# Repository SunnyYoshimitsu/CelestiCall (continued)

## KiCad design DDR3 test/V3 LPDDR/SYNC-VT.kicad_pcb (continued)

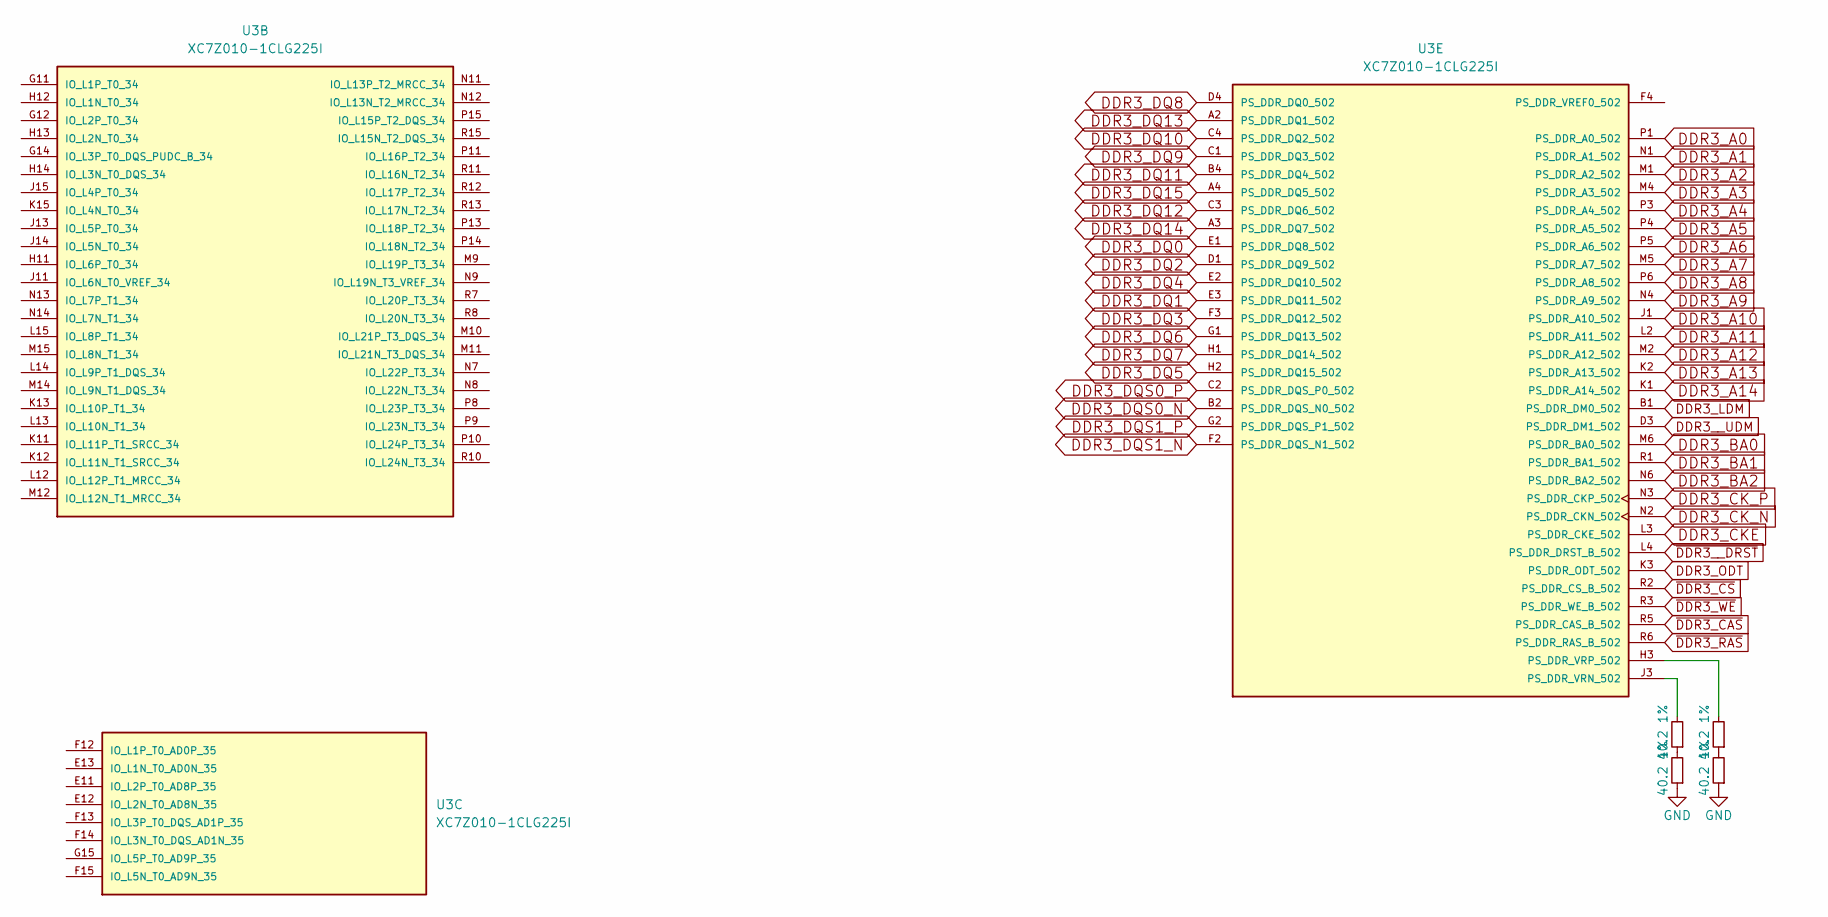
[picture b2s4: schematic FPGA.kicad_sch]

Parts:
R60, R61, R62, R63: 40.2 1%; R_0201_0603Metric; MPN RC0402FR-0740R2L
U3: XC7Z010-1CLG225I; 225-LFBGA; MPN XC7Z010-1CLG225I

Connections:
DDR3_A0: U3.P1 (PS_DDR_A0_502); also elsewhere on the board
DDR3_A1: U3.N1 (PS_DDR_A1_502); also elsewhere on the board
DDR3_A2: U3.M1 (PS_DDR_A2_502); also elsewhere on the board
DDR3_A3: U3.M4 (PS_DDR_A3_502); also elsewhere on the board
DDR3_A4: U3.P3 (PS_DDR_A4_502); also elsewhere on the board
DDR3_A5: U3.P4 (PS_DDR_A5_502); also elsewhere on the board
DDR3_A6: U3.P5 (PS_DDR_A6_502); also elsewhere on the board
DDR3_A7: U3.M5 (PS_DDR_A7_502); also elsewhere on the board
DDR3_A8: U3.P6 (PS_DDR_A8_502); also elsewhere on the board
DDR3_A9: U3.N4 (PS_DDR_A9_502); also elsewhere on the board
DDR3_A10: U3.J1 (PS_DDR_A10_502); also elsewhere on the board
DDR3_A11: U3.L2 (PS_DDR_A11_502); also elsewhere on the board
DDR3_A12: U3.M2 (PS_DDR_A12_502); also elsewhere on the board
DDR3_A13: U3.K2 (PS_DDR_A13_502); also elsewhere on the board
DDR3_A14: U3.K1 (PS_DDR_A14_502)
DDR3_BA0: U3.M6 (PS_DDR_BA0_502); also elsewhere on the board
DDR3_BA1: U3.R1 (PS_DDR_BA1_502); also elsewhere on the board
DDR3_BA2: U3.N6 (PS_DDR_BA2_502)
DDR3_CKE: U3.L3 (PS_DDR_CKE_502); also elsewhere on the board
DDR3_CK_N: U3.N2 (PS_DDR_CKN_502); also elsewhere on the board
DDR3_CK_P: U3.N3 (PS_DDR_CKP_502); also elsewhere on the board
DDR3_DQ0: U3.E1 (PS_DDR_DQ8_502); also elsewhere on the board
DDR3_DQ1: U3.E3 (PS_DDR_DQ11_502); also elsewhere on the board
DDR3_DQ2: U3.D1 (PS_DDR_DQ9_502); also elsewhere on the board
DDR3_DQ3: U3.F3 (PS_DDR_DQ12_502); also elsewhere on the board
DDR3_DQ4: U3.E2 (PS_DDR_DQ10_502); also elsewhere on the board
DDR3_DQ5: U3.H2 (PS_DDR_DQ15_502); also elsewhere on the board
DDR3_DQ6: U3.G1 (PS_DDR_DQ13_502); also elsewhere on the board
DDR3_DQ7: U3.H1 (PS_DDR_DQ14_502); also elsewhere on the board
DDR3_DQ8: U3.D4 (PS_DDR_DQ0_502); also elsewhere on the board
DDR3_DQ9: U3.C1 (PS_DDR_DQ3_502); also elsewhere on the board
DDR3_DQ10: U3.C4 (PS_DDR_DQ2_502); also elsewhere on the board
DDR3_DQ11: U3.B4 (PS_DDR_DQ4_502); also elsewhere on the board
DDR3_DQ12: U3.C3 (PS_DDR_DQ6_502); also elsewhere on the board
DDR3_DQ13: U3.A2 (PS_DDR_DQ1_502); also elsewhere on the board
DDR3_DQ14: U3.A3 (PS_DDR_DQ7_502); also elsewhere on the board
DDR3_DQ15: U3.A4 (PS_DDR_DQ5_502); also elsewhere on the board
DDR3_DQS0_N: U3.B2 (PS_DDR_DQS_N0_502)
DDR3_DQS0_P: U3.C2 (PS_DDR_DQS_P0_502); also elsewhere on the board
DDR3_DQS1_N: U3.F2 (PS_DDR_DQS_N1_502)
DDR3_DQS1_P: U3.G2 (PS_DDR_DQS_P1_502); also elsewhere on the board
DDR3_LDM: U3.B1 (PS_DDR_DM0_502); also elsewhere on the board
DDR3_ODT: U3.K3 (PS_DDR_ODT_502)
DDR3__UDM: U3.D3 (PS_DDR_DM1_502); also elsewhere on the board
GND: R61.1, R63.1; also elsewhere on the board
unnamed: R60.1, R61.2
unnamed: R62.1, R63.2
unnamed: R60.2, U3.J3 (PS_DDR_VRN_502)
unnamed: R62.2, U3.H3 (PS_DDR_VRP_502)
~DDR3_CAS: U3.R5 (PS_DDR_CAS_B_502); also elsewhere on the board
~DDR3_CS: U3.R2 (PS_DDR_CS_B_502); also elsewhere on the board
~DDR3_RAS: U3.R6 (PS_DDR_RAS_B_502); also elsewhere on the board
~DDR3_WE: U3.R3 (PS_DDR_WE_B_502); also elsewhere on the board
~DDR3__DRST: U3.L4 (PS_DDR_DRST_B_502)

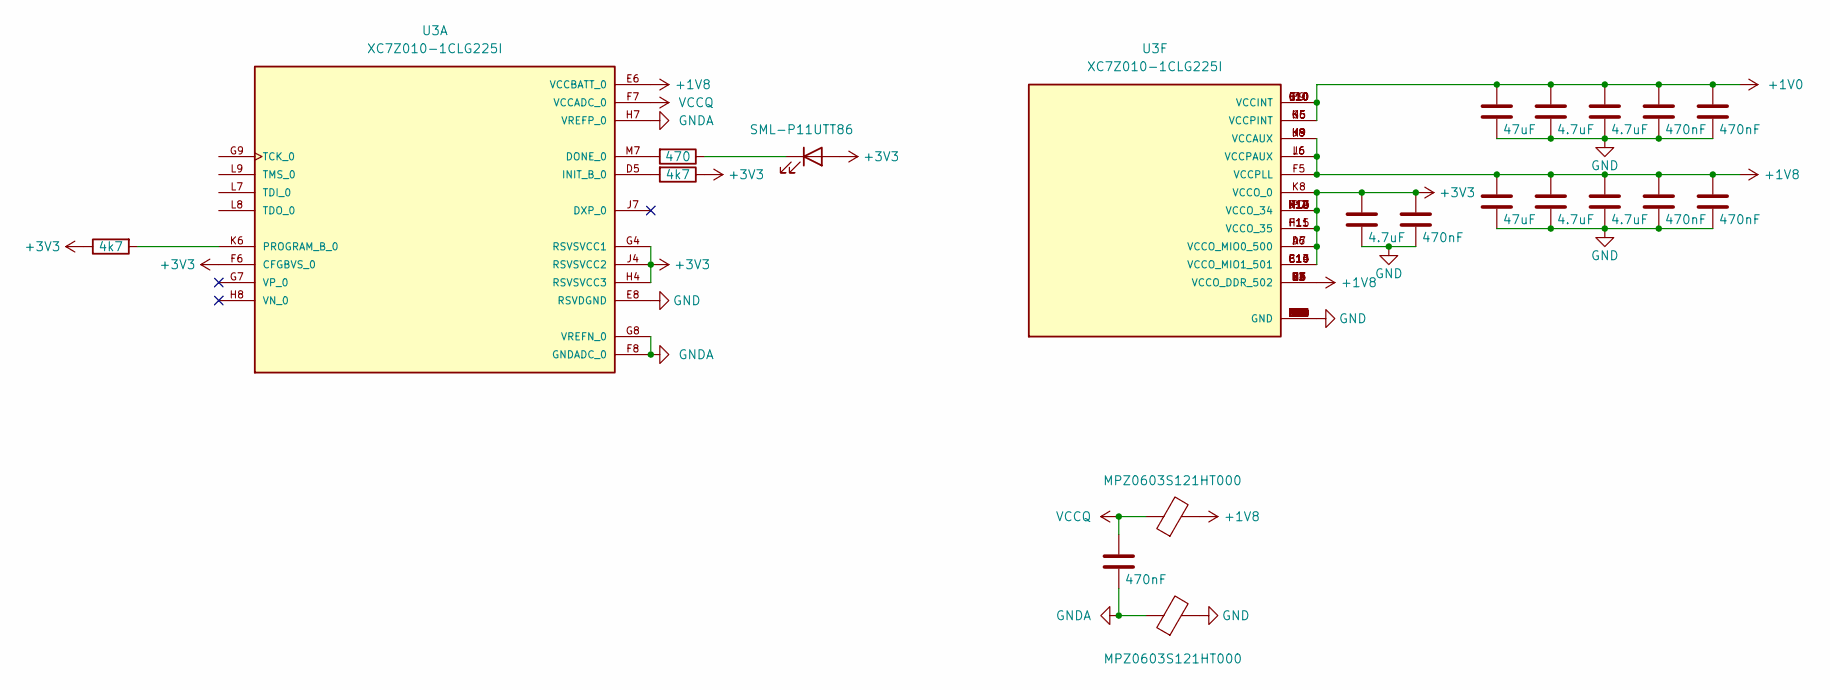
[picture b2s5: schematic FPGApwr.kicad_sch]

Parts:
C13, C19: 47uF; C_0805_2012Metric
C14, C16, C20, C21, C24: 4.7uF; C_0201_0603Metric
C15, C17, C18, C22, C23, C25: 470nF; C_0201_0603Metric
D1: SML-P11UTT86; LED_0402_1005Metric
FB1, FB2: MPZ0603S121HT000; C_0201_0603Metric
R11, R12: 4k7; C_0201_0603Metric
R13: 470; C_0201_0603Metric
U3: XC7Z010-1CLG225I; 225-LFBGA; MPN XC7Z010-1CLG225I

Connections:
+1V0: C19.1, C20.1, C21.1, C22.1, C23.1, U3.E10 (VCCINT), U3.F9 (VCCINT), U3.G6 (VCCPINT), U3.G10 (VCCINT), U3.H5 (VCCPINT), U3.J10 (VCCINT), U3.K5 (VCCPINT), U3.L10 (VCCINT); also elsewhere on the board
+1V8: C13.1, C14.1, C15.1, C16.1, C17.1, FB1.2, U3.B3 (VCCO_DDR_502), U3.E4 (VCCO_DDR_502), U3.E6 (VCCBATT_0), U3.F1 (VCCO_DDR_502), U3.F5 (VCCPLL), U3.H9 (VCCAUX), U3.J2 (VCCO_DDR_502), U3.J6 (VCCPAUX), U3.J8 (VCCAUX), U3.K9 (VCCAUX), U3.L6 (VCCPAUX), U3.M3 (VCCO_DDR_502), U3.R4 (VCCO_DDR_502); also elsewhere on the board
+3V3: C24.1, C25.1, D1.2 (A), R11.1, R12.1, U3.A6 (VCCO_MIO0_500), U3.B13 (VCCO_MIO1_501), U3.C10 (VCCO_MIO1_501), U3.D7 (VCCO_MIO0_500), U3.E14 (VCCO_MIO1_501), U3.F6 (CFGBVS_0), U3.F11 (VCCO_35), U3.G4 (RSVSVCC1), U3.H4 (RSVSVCC3), U3.H15 (VCCO_35), U3.J4 (RSVSVCC2), U3.J12 (VCCO_34), U3.K8 (VCCO_0), U3.M13 (VCCO_34), U3.N10 (VCCO_34), U3.P7 (VCCO_34), U3.R14 (VCCO_34); also elsewhere on the board
GND: C13.2, C14.2, C15.2, C16.2, C17.2, C19.2, C20.2, C21.2, C22.2, C23.2, C24.2, C25.2, FB2.2, U3.A1 (GND), U3.A11 (GND), U3.B8 (GND), U3.C5 (GND), U3.C15 (GND), U3.D2 (GND), U3.D12 (GND), U3.E5 (GND), U3.E7 (GND), U3.E8 (RSVDGND), U3.E9 (GND), U3.F10 (GND), U3.G3 (GND), U3.G5 (GND), U3.G13 (GND), U3.H6 (GND), U3.H10 (GND), U3.J5 (GND), U3.J9 (GND), U3.K4 (GND), U3.K7 (GND), U3.K10 (GND), U3.K14 (GND), U3.L1 (GND), U3.L5 (GND), U3.L11 (GND), U3.M8 (GND), U3.N5 (GND), U3.N15 (GND), U3.P2 (GND), U3.P12 (GND), U3.R9 (GND); also elsewhere on the board
GNDA: C18.2, FB2.1, U3.F8 (GNDADC_0), U3.G8 (VREFN_0), U3.H7 (VREFP_0)
unnamed: D1.1 (K), R13.1
unnamed: R13.2, U3.M7 (DONE_0)
unnamed: R11.2, U3.D5 (INIT_B_0)
unnamed: R12.2, U3.K6 (PROGRAM_B_0)
VCCQ: C18.1, FB1.1, U3.F7 (VCCADC_0)

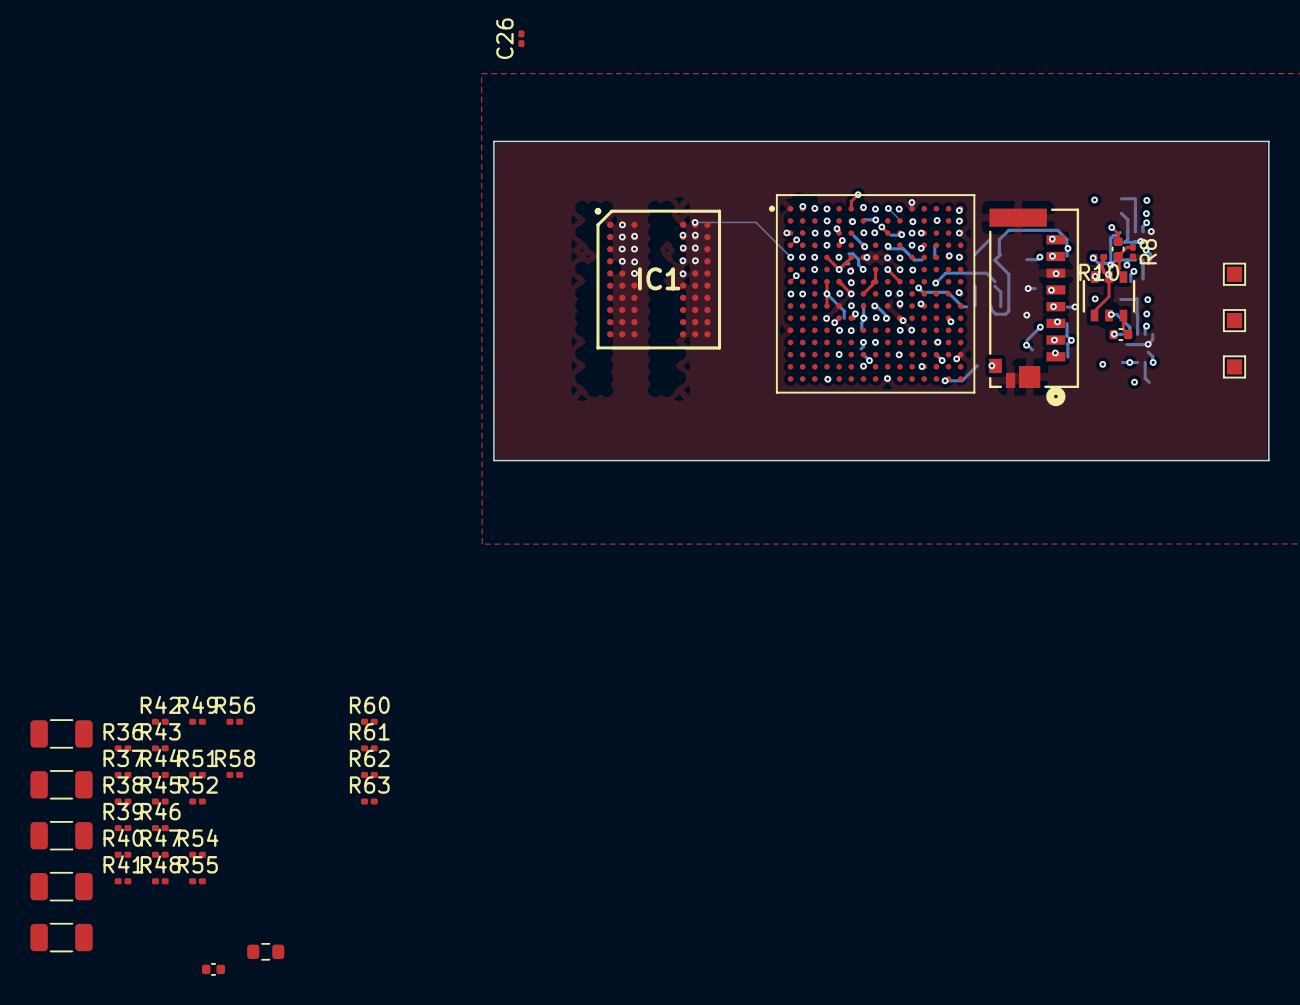
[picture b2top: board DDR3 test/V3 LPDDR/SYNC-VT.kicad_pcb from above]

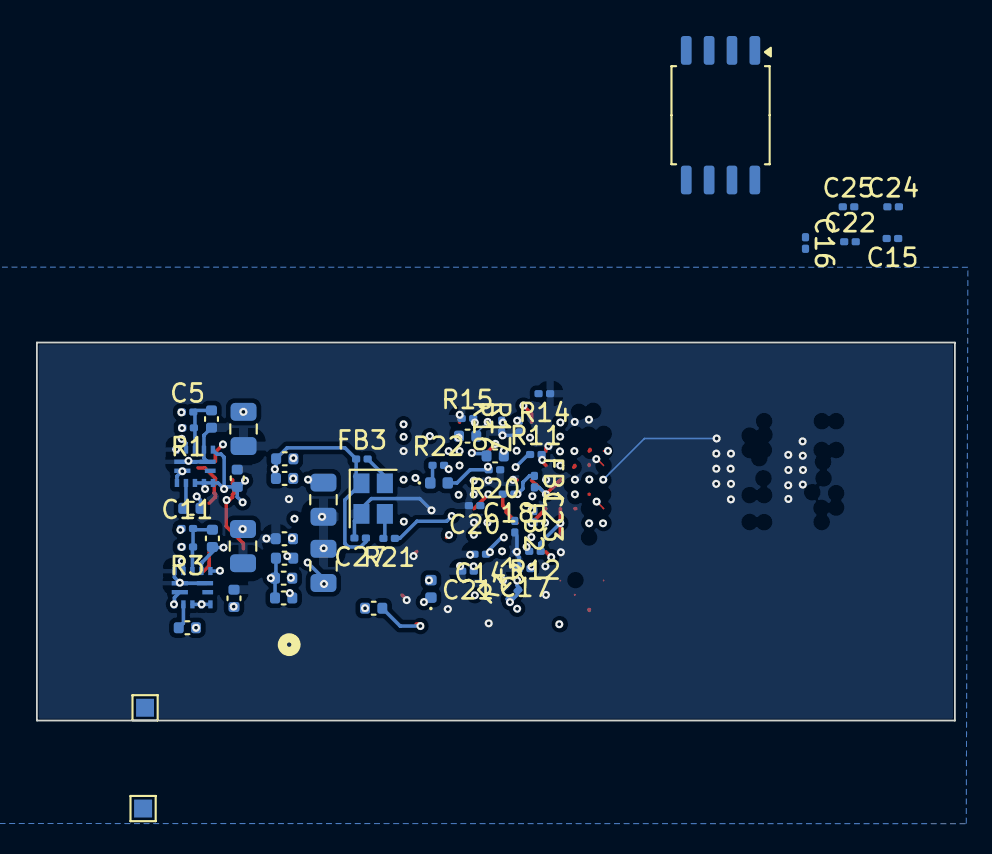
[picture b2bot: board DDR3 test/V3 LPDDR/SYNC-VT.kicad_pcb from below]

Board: 6 copper layers, 51.0 x 21.0 mm, 99 parts (56 on the bottom side), 85 nets.

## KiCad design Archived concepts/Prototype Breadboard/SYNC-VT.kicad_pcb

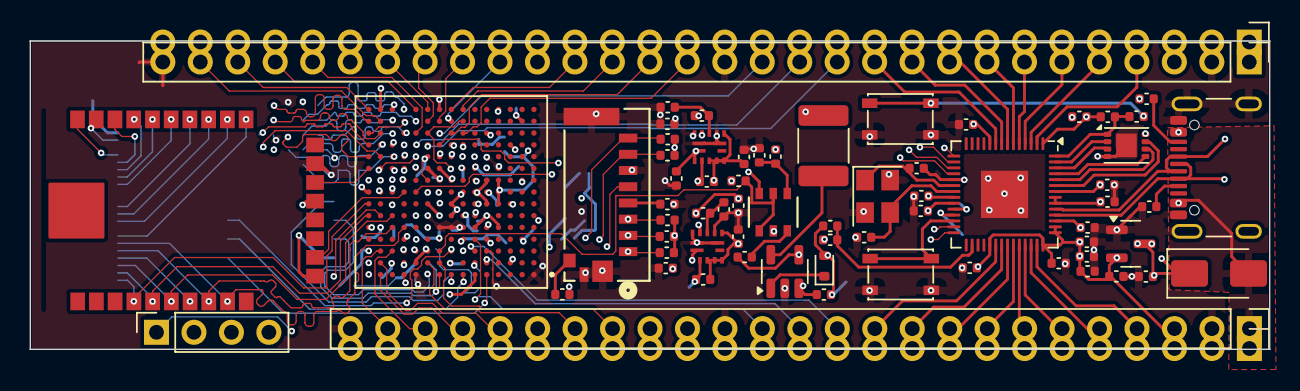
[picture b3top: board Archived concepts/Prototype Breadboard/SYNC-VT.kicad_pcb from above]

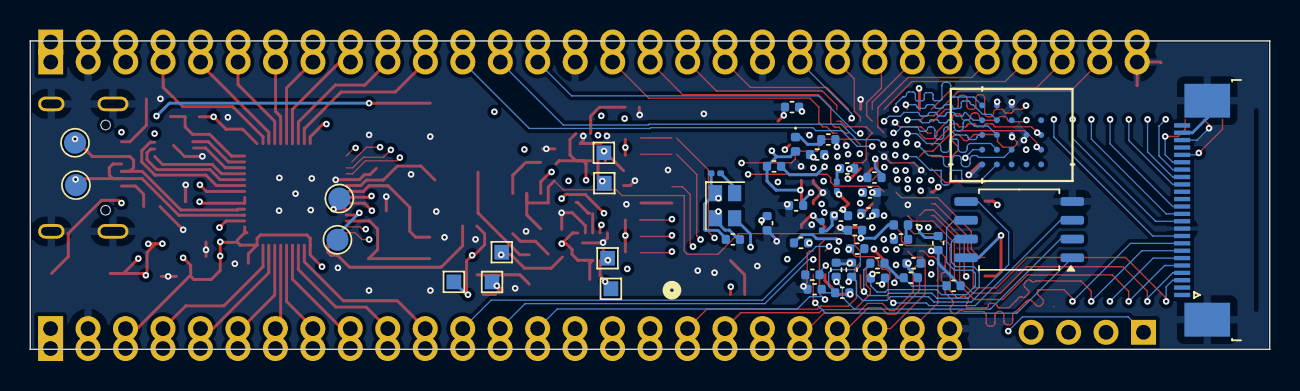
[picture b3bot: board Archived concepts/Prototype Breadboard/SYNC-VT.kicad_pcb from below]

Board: 6 copper layers, 84.0 x 20.9 mm, 115 parts (47 on the bottom side), 142 nets.

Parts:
C1, C5, C8, C9, C10, C11, C12: 22uF; C_0402_1005Metric
C2, C3: 22pF; C_0402_1005Metric
C4, C6, C7, C14, C15, C16, C17, C18, C20, C21, C22, C24, C25, C26, C27, C28, C29, C30, C31, C32, C33, C34, C35, C36, C37, C38: 4.7uF; C_0402_1005Metric
D1, D2: SML-P11UTT86; LED_0402_1005Metric
D3: SOD-523 General; D_SOD-523
D4: SOD-523 General; D_SMA
FB1, FB2, FB3: MPZ0603S121HT000; C_0201_0603Metric
FLASH1: W25Q16JVUXIQ; SON-8-1EP_3x2mm_P0.5mm_EP1.4x1.6mm
J1, J2: Button; SW_SPST_PTS810
J3, J7: Conn_01x30_MountingPin; PinHeader_1x30_P2.54mm_Vertical
J4, J5: Conn_01x25_MountingPin; PinHeader_1x25_P2.54mm_Vertical
J6: Conn_01x04_MountingPin; PinSocket_1x04_P2.54mm_Vertical
J8: Conn_01x24_MountingPin; TE_2-1734839-4_1x24-1MP_P0.5mm_Horizontal
L1: 2.2uH; C_1812_4532Metric
R1, R3, R8, R10, R14, R20, R36: 20k; C_0402_1005Metric
R2: 30k; C_0402_1005Metric
R4, R5, R6, R7, R9, R11, R12, R13, R15, R16, R17, R18, R19, R21, R22, R23, R24, R25, R26, R27, R28, R32, R33, R34, R35, R37, R38, R40: 10k; C_0402_1005Metric
R41, R42: DNP; C_0402_1005Metric
TP1, TP2, TP3, TP4, TP5, TP10, TP11: TP; TestPoint_Pad_1.0x1.0mm
TP6, TP7, TP8, TP9: TestPoint; TestPoint_Pad_D1.5mm
U1, U2: MPM3834CGPA-Z; ECLGA-14_MPM3834C_MNP
U3: XC7Z010-1CLG225I; 225-LFBGA
U4: TPS3106K33DBVR; DBV6-L
U5: W25Q128JVS; SOIC-8_5.23x5.23mm_P1.27mm
U6: 0473092651; CONN12_47309-2651_MOL
U7: S80KS5123GABHA020; PG-BGA-24-801
U8: ZL6201A33S3; SOT-23
U9: RP2040; QFN-56-1EP_7x7mm_P0.4mm_EP3.2x3.2mm
U10: NanoS3
U11: SC189ZULTRT-3v3; SOT-23-5
USB_C_ESP1: USB_C_1; USB_C_Receptacle_GCT_USB4105-xx-A_16P_TopMnt_Horizontal
X1: SIT8008BI-73-XXS-33.333333; Oscillator_SMD_SeikoEpson_SG210-4Pin_2.5x2.0mm
Y1: 3225-4P 12MHz; Crystal_SMD_3225-4Pin_3.2x2.5mm

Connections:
33.33Mhz: U3.C7 (PS_CLK_500), X1.3 (OUT)
+1V0: C9.2, C11.2, C20.1, C21.1, C22.1, R1.2, R9.2, TP5.1, U1.6 (OUT_S), U1.9 (OUT), U1.10 (OUT), U3.E10 (VCCINT), U3.F9 (VCCINT), U3.G6 (VCCPINT), U3.G10 (VCCINT), U3.H5 (VCCPINT), U3.J10 (VCCINT), U3.K5 (VCCPINT), U3.L10 (VCCINT)
+1V1: C4.1, C6.1, C7.1, U9.23 (DVDD), U9.45 (VREG_VOUT), U9.50 (DVDD)
+1V8: C5.2, C12.2, C14.1, C15.1, C16.1, C17.1, FB1.2, R3.2, TP4.1, U2.6 (OUT_S), U2.9 (OUT), U2.10 (OUT), U3.B3 (VCCO_DDR_502), U3.E4 (VCCO_DDR_502), U3.E6 (VCCBATT_0), U3.F1 (VCCO_DDR_502), U3.F5 (VCCPLL), U3.H9 (VCCAUX), U3.J2 (VCCO_DDR_502), U3.J6 (VCCPAUX), U3.J8 (VCCAUX), U3.K9 (VCCAUX), U3.L6 (VCCPAUX), U3.M3 (VCCO_DDR_502), U3.R4 (VCCO_DDR_502)
+2V8: J8.14, J8.21
+3.3VA: C28.1, C29.1, C30.1, C31.1, C32.1, C33.1, C34.1, C35.1, C37.1, C38.1, FLASH1.8 (VCC), J3.3, J4.3, J5.3, J7.3, R37.1, U8.2 (VO), U9.1 (IOVDD), U9.10 (IOVDD), U9.22 (IOVDD), U9.33 (IOVDD), U9.42 (IOVDD), U9.43 (ADC_AVDD), U9.44 (VREG_IN), U9.48 (USB_VDD), U9.49 (IOVDD)
+3V3: C24.1, C25.1, C26.1, C27.1, D1.2 (A), FB3.1, L1.2, R7.2, R10.2, R12.1, R13.2, R21.1, R23.1, R24.1, R25.1, R26.1, R27.1, R28.1, R40.1, TP3.1, U3.A6 (VCCO_MIO0_500), U3.B11 (PS_SRST_B_501), U3.B13 (VCCO_MIO1_501), U3.C10 (VCCO_MIO1_501), U3.D7 (VCCO_MIO0_500), U3.E14 (VCCO_MIO1_501), U3.F6 (CFGBVS_0), U3.F11 (VCCO_35), U3.G4 (RSVSVCC1), U3.H4 (RSVSVCC3), U3.H15 (VCCO_35), U3.J4 (RSVSVCC2), U3.J12 (VCCO_34), U3.K8 (VCCO_0), U3.M13 (VCCO_34), U3.N10 (VCCO_34), U3.P7 (VCCO_34), U3.R14 (VCCO_34), U4.6 (VDD), U5.8 (VCC), U7.B4 (VCC), U7.D1 (VCCQ), U7.E4 (VCCQ), U10.8 (3v3), U11.4 (VOUT), X1.1 (OE)
+5VD: C8.1, C10.1, C36.2, D4.1 (K), R4.2, R6.2, U1.3 (EN), U1.12 (IN), U1.13 (IN), U1.14 (IN), U2.3 (EN), U2.12 (IN), U2.13 (IN), U2.14 (IN), U8.3 (VI)
/Peripheral/RUN: J1.1, U9.26 (RUN)
/Peripheral/SWCLK: TP8.1, U9.24 (SWCLK)
/Peripheral/SWD: TP9.1, U9.25 (SWD)
AIO0N: J8.7, U3.E13 (IO_L1N_T0_AD0N_35), U10.11 (IO18)
AIO3N: J8.6, U3.F14 (IO_L3N_T0_DQS_AD1N_35), U10.12 (IO17)
AIO3P: J8.5, U3.F13 (IO_L3P_T0_DQS_AD1P_35), U10.13 (IO16)
AIO5N: J8.4, U3.F15 (IO_L5N_T0_AD9N_35), U10.14 (IO15)
AIO5P: J8.3, U3.G15 (IO_L5P_T0_AD9P_35), U10.15 (IO14)
AIO8N: J8.8, U3.E12 (IO_L2N_T0_AD8N_35), U10.10 (IO21)
GND: C1.2, C2.2, C3.2, C4.2, C5.1, C6.2, C7.2, C8.2, C9.1, C10.2, C11.1, C12.1, C14.2, C15.2, C16.2, C17.2, C20.2, C21.2, C22.2, C24.2, C25.2, C26.2, C27.2, C28.2, C29.2, C30.2, C31.2, C32.2, C33.2, C34.2, C35.2, C36.1, C37.2, C38.2, FB2.2, FLASH1.4 (GND), FLASH1.9 (EP), J1.2, J2.2, J3.2, J3.15, J3.20, J3.25, J3.30, J4.2, J4.15, J4.20, J4.25, J5.2, J5.15, J5.20, J5.25, J7.2, J7.15, J7.20, J7.25, J7.30, J8.10, J8.23, J8.MP (MountPin), R2.1, R5.1, R8.2, R14.1, R15.1, R16.1, R17.1, R20.1, R22.1, R33.2, R34.2, R36.1, R41.1, R42.1, U1.2 (PGND), U1.4 (AGND), U1.7 (PGND), U1.8 (PGND), U2.2 (PGND), U2.4 (AGND), U2.7 (PGND), U2.8 (PGND), U3.A1 (GND), U3.A11 (GND), U3.B8 (GND), U3.C5 (GND), U3.C15 (GND), U3.D2 (GND), U3.D12 (GND), U3.E5 (GND), U3.E7 (GND), U3.E8 (RSVDGND), U3.E9 (GND), U3.F10 (GND), U3.G3 (GND), U3.G5 (GND), U3.G13 (GND), U3.H6 (GND), U3.H10 (GND), U3.J5 (GND), U3.J9 (GND), U3.K4 (GND), U3.K7 (GND), U3.K10 (GND), U3.K14 (GND), U3.L1 (GND), U3.L5 (GND), U3.L11 (GND), U3.M8 (GND), U3.N5 (GND), U3.N15 (GND), U3.P2 (GND), U3.P12 (GND), U3.R9 (GND), U4.2 (GND), U5.4 (GND), U6.6, U6.G1, U6.G2, U6.G3, U7.B3 (VSS), U7.C1 (VSSQ), U7.E5 (VSSQ), U8.1 (GND), U9.19 (TESTEN), U9.57 (GND), U10.2 (GND), U11.2 (GND), USB_C_ESP1.A1 (GND), USB_C_ESP1.A12 (GND), USB_C_ESP1.B1 (GND), USB_C_ESP1.B12 (GND), USB_C_ESP1.S1 (SHIELD), X1.2 (GND), Y1.2, Y1.4
GNDA: C18.2, FB2.1, U3.F8 (GNDADC_0), U3.G8 (VREFN_0), U3.H7 (VREFP_0)
GPIO0: J3.4, J7.4, U9.2 (GPIO0)
GPIO1: J3.5, J7.5, U9.3 (GPIO1)
GPIO2: J3.6, J7.6, U9.4 (GPIO2)
GPIO3: J3.7, J7.7, U9.5 (GPIO3)
GPIO4: J3.8, J7.8, U9.6 (GPIO4)
GPIO5: J3.9, J7.9, U9.7 (GPIO5)
GPIO6: J3.10, J7.10, U9.8 (GPIO6)
GPIO7: J3.11, J7.11, U9.9 (GPIO7)
GPIO12: J6.2, U3.L9 (TMS_0), U9.15 (GPIO12)
GPIO13: J6.3, U3.L8 (TDO_0), U9.16 (GPIO13)
GPIO14: J6.4, U3.L7 (TDI_0), U9.17 (GPIO14)
GPIO15: J6.1, U3.G9 (TCK_0), U9.18 (GPIO15)
GPIO16: U3.M9 (IO_L19P_T3_34), U9.27 (GPIO16)
GPIO17: U3.H11 (IO_L6P_T0_34), U9.28 (GPIO17)
GPIO19: R35.1, R36.2, U9.30 (GPIO19)
GPIO22: J4.11, J5.11, U9.34 (GPIO22)
GPIO23: J4.10, J5.10, U9.35 (GPIO23)
GPIO24: J4.9, J5.9, U9.36 (GPIO24)
GPIO25: J4.8, J5.8, U9.37 (GPIO25)
GPIO26: J4.7, J5.7, U9.38 (GPIO26_ADC0)
GPIO27: J4.6, J5.6, U9.39 (GPIO27_ADC1)
GPIO28: J4.5, J5.5, U9.40 (GPIO28_ADC2)
GPIO29: J4.4, J5.4, U9.41 (GPIO29_ADC3)
IO1N: U3.H12 (IO_L1N_T0_34), U10.7 (EN)
IO2N: J8.17, U3.H13 (IO_L2N_T0_34), U10.28 (IO8)
IO3N: J8.16, U3.H14 (IO_L3N_T0_DQS_34), U10.27 (IO9)
IO4N: U3.K15 (IO_L4N_T0_34), U10.3 (RESET)
IO4P: J8.13, U3.J15 (IO_L4P_T0_34), U10.26 (IO34)
IO5N: J8.12, U3.J14 (IO_L5N_T0_34), U10.25 (IO36)
IO5P: J8.11, U3.J13 (IO_L5P_T0_34), U10.24 (IO37)
IO10P: J8.9, U3.K13 (IO_L10P_T1_34), U10.23 (IO35)
IO11N: J8.22, U3.K12 (IO_L11N_T1_SRCC_34), U10.31 (RX)
IO11P: J8.20, U3.K11 (IO_L11P_T1_SRCC_34), U10.32 (TX)
IO12N: J8.18, U3.M12 (IO_L12N_T1_MRCC_34), U10.29 (IO0)
IO12P: J8.19, U3.L12 (IO_L12P_T1_MRCC_34), U10.30 (IO33)
IO13P: J3.26, J7.26, U3.N11 (IO_L13P_T2_MRCC_34)
IO15N: J3.28, J7.28, U3.R15 (IO_L15N_T2_DQS_34)
IO16N: J3.27, J7.27, U3.R11 (IO_L16N_T2_34)
IO18N: J3.29, J7.29, U3.P14 (IO_L18N_T2_34)
IO19N: J3.14, J7.14, U3.N9 (IO_L19N_T3_VREF_34)
IO20N: J3.19, J7.19, U3.R8 (IO_L20N_T3_34)
IO20P: J3.18, J7.18, U3.R7 (IO_L20P_T3_34)
IO21N: J3.13, J7.13, U3.M11 (IO_L21N_T3_DQS_34)
IO21P: J3.12, J7.12, U3.M10 (IO_L21P_T3_DQS_34)
IO22N: J3.17, J7.17, U3.N8 (IO_L22N_T3_34)
IO22P: J3.16, J7.16, U3.N7 (IO_L22P_T3_34)
IO23N: J3.22, J7.22, U3.P9 (IO_L23N_T3_34)
IO23P: J3.21, J7.21, U3.P8 (IO_L23P_T3_34)
IO24N: J3.24, J7.24, U3.R10 (IO_L24N_T3_34)
IO24P: J3.23, J7.23, U3.P10 (IO_L24P_T3_34)
MIO7: D2.2 (A), R20.2, U3.D9 (PS_MIO7_500)
MIO9: J4.13, J5.13, U3.B5 (PS_MIO9_500)
MIO10: J4.14, J5.14, U3.D6 (PS_MIO10_500)
MIO11: J4.19, J5.19, U3.B10 (PS_MIO11_500)
MIO13: J4.12, J5.12, U3.C6 (PS_MIO13_500)
MIO14: J4.18, J5.18, U3.B9 (PS_MIO14_500)
MIO28: U3.A15 (PS_MIO28_501), U6.5
MIO29: R26.2, U3.D11 (PS_MIO29_501), U6.3
MIO30: R27.2, U3.B15 (PS_MIO30_501), U6.7
MIO31: R28.2, U3.C12 (PS_MIO31_501), U6.8
MIO32: R24.2, U3.E15 (PS_MIO32_501), U6.1
MIO33: R25.2, U3.C11 (PS_MIO33_501), U6.2
MIO35: J4.22, J5.22, U3.A14 (PS_MIO35_501)
MIO36: J4.21, J5.21, U3.B14 (PS_MIO36_501)
MIO37: J4.24, J5.24, U3.C14 (PS_MIO37_501)
MIO48: J4.16, J5.16, U3.B12 (PS_MIO48_501)
MIO52: J4.17, J5.17, U3.A12 (PS_MIO52_501)
MIO53: J4.23, J5.23, U3.C13 (PS_MIO53_501)
unnamed: C1.1, U6.4
unnamed: D1.1 (K), R11.1
unnamed: D2.1 (K), R22.2
unnamed: D3.1 (K), U11.1 (VIN)
unnamed: J2.1, R32.2
unnamed: R18.1, R21.2, R41.2
unnamed: R19.1, R40.2, R42.2
unnamed: R23.2, U6.G4
unnamed: R6.1, TP1.1, U2.11 (PG)
unnamed: R4.1, TP2.1, U1.11 (PG)
unnamed: R38.2, TP11.1, U11.3 (EN)
unnamed: R1.1, R2.2, U1.5 (FB)
unnamed: R3.1, R5.2, U2.5 (FB)
unnamed: R11.2, U3.M7 (DONE_0)
unnamed: R12.2, U3.D5 (INIT_B_0)
unnamed: R13.1, U3.K6 (PROGRAM_B_0)
unnamed: R14.2, U3.B6 (PS_MIO8_500)
unnamed: R8.1, R9.1, U4.4 (SENSE)
unnamed: C2.1, U9.20 (XIN), Y1.1
unnamed: C3.1, U9.21 (XOUT), Y1.3
unnamed: L1.1, U11.5 (LX)
unnamed: R33.1, USB_C_ESP1.A5 (CC1)
unnamed: R34.1, USB_C_ESP1.B5 (CC2)
unnamed: FB3.2, X1.4 (Vcc)
POR_B: R10.1, U3.C9 (PS_POR_B_500), U4.1 (*RSTVDD), U4.5 (*RSTSENSE)
QSPI_SCLK: FLASH1.6 (CLK), U9.52 (QSPI_SCLK)
QSPI_SD0: FLASH1.5 (DI(IO0)), U9.53 (QSPI_SD0)
QSPI_SD1: FLASH1.2 (DO(IO1)), U9.55 (QSPI_SD1)
QSPI_SD2: FLASH1.3 (IO2), U9.54 (QSPI_SD2)
QSPI_SD3: FLASH1.7 (IO3), U9.51 (QSPI_SD3)
QSPI_SS: FLASH1.1 (~CS), R32.1, R37.2, U9.56 (QSPI_SS)
RAM_CLK: U3.N14 (IO_L7N_T1_34), U7.B2 (CK)
RAM_DQ0: U3.P13 (IO_L18P_T2_34), U7.D3 (DQ0)
RAM_DQ1: U3.R13 (IO_L17N_T2_34), U7.D2 (DQ1)
RAM_DQ2: U3.M14 (IO_L9N_T1_DQS_34), U7.C4 (DQ2)
RAM_DQ3: U3.N13 (IO_L7P_T1_34), U7.D4 (DQ3)
RAM_DQ4: U3.L13 (IO_L10N_T1_34), U7.D5 (DQ4)
RAM_DQ5: U3.N12 (IO_L13N_T2_MRCC_34), U7.E3 (DQ5)
RAM_DQ6: U3.P11 (IO_L16P_T2_34), U7.E2 (DQ6)
RAM_DQ7: U3.R12 (IO_L17P_T2_34), U7.E1 (DQ7)
RWDS: U3.L15 (IO_L8P_T1_34), U7.C3 (RWDS)
SPI-CLK: R15.2, U3.A10 (PS_MIO6_500), U5.6 (CLK)
SPI-CS: U3.A5 (PS_MIO1_500), U5.1 (~CS)
SPI-D0: R16.2, U3.A8 (PS_MIO2_500), U5.5 (DI(IO0))
SPI-D1: R17.2, U3.A7 (PS_MIO3_500), U5.2 (DO(IO1))
SPI-D2: R18.2, U3.C8 (PS_MIO4_500), U5.3 (IO2)
SPI-D3: R19.2, U3.A9 (PS_MIO5_500), U5.7 (IO3)
USB_D+0: TP6.1, U9.47 (USB_DP), USB_C_ESP1.A6 (D+), USB_C_ESP1.B6 (D+)
USB_D-0: TP7.1, U9.46 (USB_DM), USB_C_ESP1.A7 (D-), USB_C_ESP1.B7 (D-)
VBUS0: D3.2 (A), D4.2 (A), J3.1, J4.1, J5.1, J7.1, R35.2, R38.1, TP10.1, U10.4 (5V), USB_C_ESP1.A4 (VBUS), USB_C_ESP1.A9 (VBUS), USB_C_ESP1.B4 (VBUS), USB_C_ESP1.B9 (VBUS)
VCCQ: C18.1, FB1.1, U3.F7 (VCCADC_0)
~RAM_CLK: U3.P15 (IO_L15P_T2_DQS_34), U7.B1 (CK#)
~RAM_CS0: U3.M15 (IO_L8N_T1_34), U7.A3 (CS#)
~RAM_RST: U3.L14 (IO_L9P_T1_DQS_34), U7.A4 (RESET#)
~RST: R7.1, U4.3 (*MR)

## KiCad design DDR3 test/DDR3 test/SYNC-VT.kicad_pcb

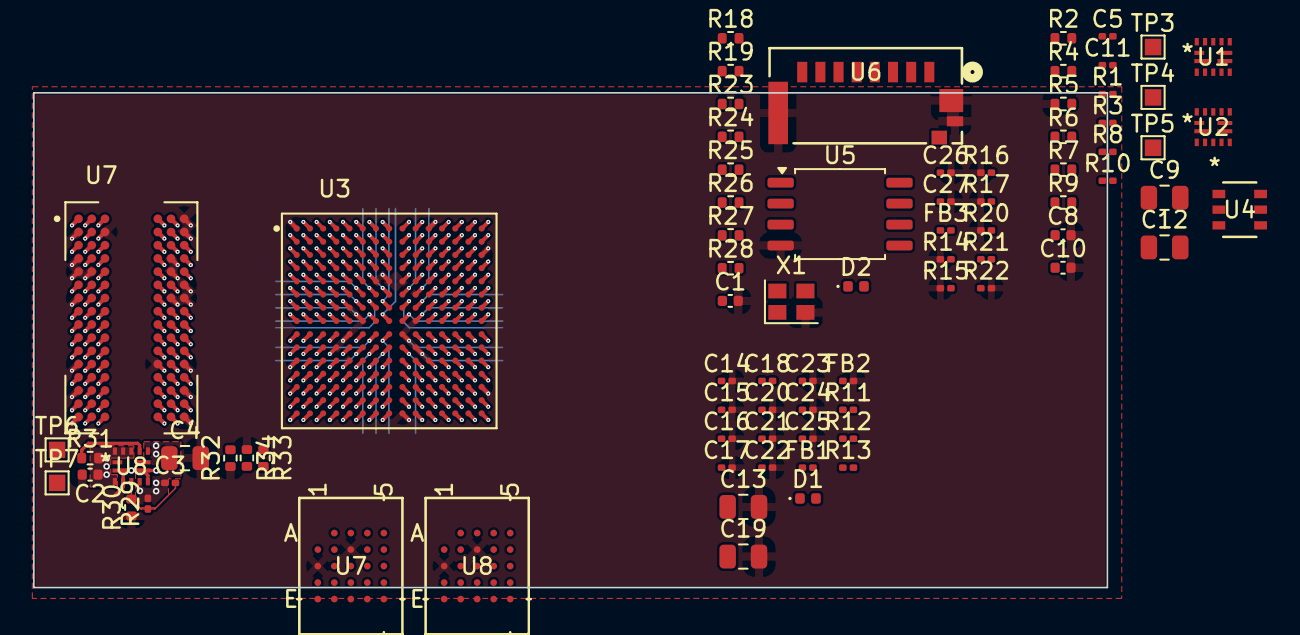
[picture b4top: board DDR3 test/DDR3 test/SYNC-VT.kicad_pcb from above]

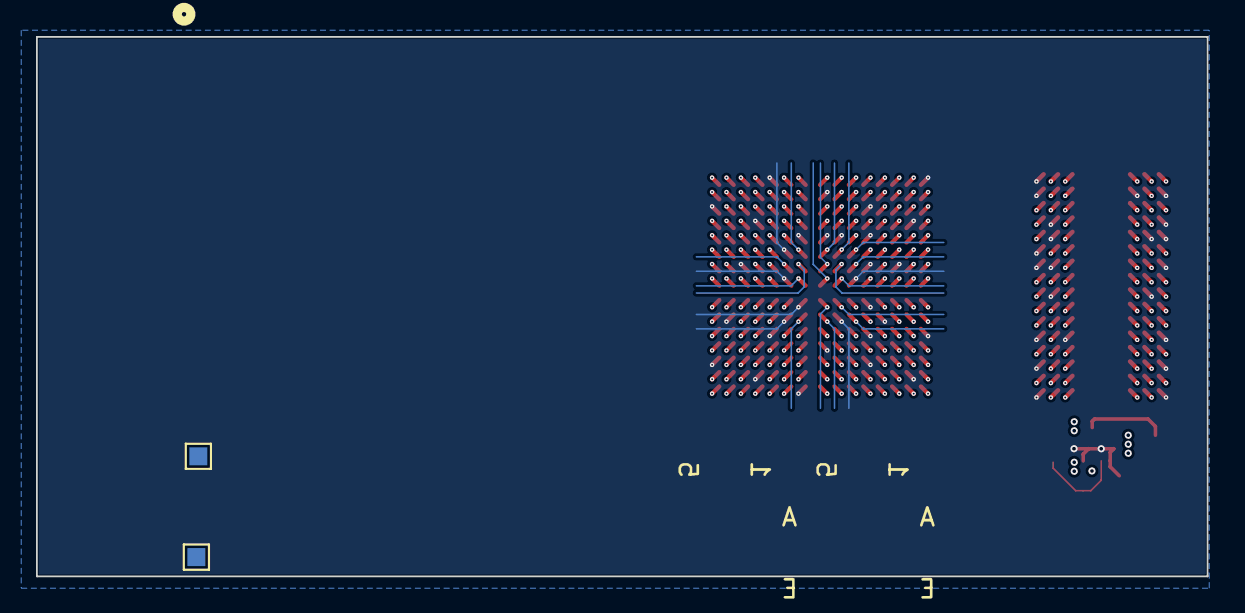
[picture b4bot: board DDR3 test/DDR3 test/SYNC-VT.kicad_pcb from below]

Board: 6 copper layers, 65.0 x 30.0 mm, 82 parts (2 on the bottom side), 105 nets.

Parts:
C1, C2, C8, C10: 22uF; C_0402_1005Metric
C3, C5, C11: 10pF; C_0201_0603Metric
C4, C9, C12, C13, C19: 47uF; C_0805_2012Metric
C14, C16, C20, C21, C24: 4.7uF; C_0201_0603Metric
C15, C17, C18, C22, C23, C25, C26, C27: 470nF; C_0201_0603Metric
D1, D2: SML-P11UTT86; LED_0402_1005Metric
FB1, FB2, FB3: MPZ0603S121HT000; C_0201_0603Metric
R1, R3, R8, R10, R14, R15, R16, R17, R20, R29: 20k; R_0201_0603Metric
R2: 30k; R_0402_1005Metric
R4, R5, R6, R7, R9, R18, R19, R23, R24, R25, R26, R27, R28, R31: 10k; R_0402_1005Metric
R11, R12: 4k7; R_0201_0603Metric
R13, R22: 470; R_0201_0603Metric
R21: 33; R_0201_0603Metric
R30: 13.3k; R_0402_1005Metric
R32: 240; R_0402_1005Metric
R33, R34: 80; R_0402_1005Metric
TP1, TP2, TP3, TP4, TP5, TP6, TP7: TP; TestPoint_Pad_1.0x1.0mm
U1, U2, U8#2: MPM3834CGPA-Z; ECLGA-14_MPM3834C_MNP
U3: XC7Z010-1CLG225I; BGA225C80P15X15_1300X1300X150N
U4: TPS3106K33DBVR; DBV6-L
U5: W25Q128JVS; SOIC-8_5.23x5.23mm_P1.27mm
U6: 0473092651; CONN12_47309-2651_MOL
U7: MT41K512M16VRP-107_IT_P_TR; IC_MT41K512M16VRP-107_IT_P_TR
U7#2, U8: S80KS5123GABHA020; PG-BGA-24-801
X1: SIT8008BI-73-XXS-33.333333; Oscillator_SMD_SeikoEpson_SG210-4Pin_2.5x2.0mm

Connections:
33.33Mhz: R21.2, X1.3 (OUT)
+1V0: C5.1, C9.1, C19.1, C20.1, C21.1, C22.1, C23.1, R1.2, R9.2, TP5.1, U1.6 (OUT_S), U1.9 (OUT), U1.10 (OUT), U3.E10 (VCCINT), U3.F9 (VCCINT), U3.G6 (VCCPINT), U3.G10 (VCCINT), U3.H5 (VCCPINT), U3.J10 (VCCINT), U3.K5 (VCCPINT), U3.L10 (VCCINT)
+1V5: C3.1, C4.1, R29.2, TP7.1, U7.A1 (VDDQ), U7.A8 (VDDQ), U7.B2 (VDD), U7.C1 (VDDQ), U7.C9 (VDDQ), U7.D2 (VDDQ), U7.D9 (VDD), U7.E9 (VDDQ), U7.F1 (VDDQ), U7.G7 (VDD), U7.H2 (VDDQ), U7.H9 (VDDQ), U7.K2 (VDD), U7.K8 (VDD), U7.N1 (VDD), U7.N9 (VDD), U7.R1 (VDD), U7.R9 (VDD), U8#2.6 (OUT_S), U8#2.9 (OUT), U8#2.10 (OUT)
+1V8: C11.1, C12.1, C13.1, C14.1, C15.1, C16.1, C17.1, FB1.2, R3.2, TP4.1, U2.6 (OUT_S), U2.9 (OUT), U2.10 (OUT), U3.B3 (VCCO_DDR_502), U3.E4 (VCCO_DDR_502), U3.E6 (VCCBATT_0), U3.F1 (VCCO_DDR_502), U3.F5 (VCCPLL), U3.H9 (VCCAUX), U3.J2 (VCCO_DDR_502), U3.J6 (VCCPAUX), U3.J8 (VCCAUX), U3.K9 (VCCAUX), U3.L6 (VCCPAUX), U3.M3 (VCCO_DDR_502), U3.R4 (VCCO_DDR_502)
+3V3: C2.1, C8.1, C10.1, C24.1, C25.1, C26.1, C27.1, D1.2 (A), FB3.1, R4.2, R6.2, R7.2, R10.2, R11.1, R12.1, R18.1, R19.1, R23.1, R24.1, R25.1, R26.1, R27.1, R28.1, R31.2, TP3.1, U1.3 (EN), U1.12 (IN), U1.13 (IN), U1.14 (IN), U2.3 (EN), U2.12 (IN), U2.13 (IN), U2.14 (IN), U3.A6 (VCCO_MIO0_500), U3.B11 (PS_SRST_B_501), U3.B13 (VCCO_MIO1_501), U3.C10 (VCCO_MIO1_501), U3.D7 (VCCO_MIO0_500), U3.E14 (VCCO_MIO1_501), U3.F6 (CFGBVS_0), U3.F11 (VCCO_35), U3.G4 (RSVSVCC1), U3.H4 (RSVSVCC3), U3.H15 (VCCO_35), U3.J4 (RSVSVCC2), U3.J12 (VCCO_34), U3.K8 (VCCO_0), U3.M13 (VCCO_34), U3.N10 (VCCO_34), U3.P7 (VCCO_34), U3.R14 (VCCO_34), U4.6 (VDD), U5.8 (VCC), U7#2.B4 (VCC), U7#2.D1 (VCCQ), U7#2.E4 (VCCQ), U8.B4 (VCC), U8.D1 (VCCQ), U8.E4 (VCCQ), U8#2.3 (EN), U8#2.12 (IN), U8#2.13 (IN), U8#2.14 (IN), X1.1 (OE)
/RAM/CK: U3.N3 (PS_DDR_CKP_502), U7.J7 (CK)
/RAM/CKE: U3.L3 (PS_DDR_CKE_502), U7.K9 (CKE)
/RAM/DDR_A0: U3.P1 (PS_DDR_A0_502), U7.N3 (A0)
/RAM/DDR_A1: U3.N1 (PS_DDR_A1_502), U7.P7 (A1)
/RAM/DDR_A2: U3.M1 (PS_DDR_A2_502), U7.P3 (A2)
/RAM/DDR_A3: U3.M4 (PS_DDR_A3_502), U7.N2 (A3)
/RAM/DDR_A4: U3.P3 (PS_DDR_A4_502), U7.P8 (A4)
/RAM/DDR_A5: U3.P4 (PS_DDR_A5_502), U7.P2 (A5)
/RAM/DDR_A6: U3.P5 (PS_DDR_A6_502), U7.R8 (A6)
/RAM/DDR_A7: U3.M5 (PS_DDR_A7_502), U7.R2 (A7)
/RAM/DDR_A8: U3.P6 (PS_DDR_A8_502), U7.T8 (A8)
/RAM/DDR_A9: U3.N4 (PS_DDR_A9_502), U7.R3 (A9)
/RAM/DDR_A10: U3.J1 (PS_DDR_A10_502), U7.L7 (A10/AP)
/RAM/DDR_A11: U3.L2 (PS_DDR_A11_502), U7.R7 (A11)
/RAM/DDR_A12: U3.M2 (PS_DDR_A12_502), U7.N7 (A12/~BC)
/RAM/DDR_A13: U3.K2 (PS_DDR_A13_502), U7.T3 (A13)
/RAM/DDR_A14: U3.K1 (PS_DDR_A14_502), U7.T7 (A14)
/RAM/DDR_BA0: U3.M6 (PS_DDR_BA0_502), U7.M2 (BA0)
/RAM/DDR_BA1: U3.R1 (PS_DDR_BA1_502), U7.N8 (BA1)
/RAM/DDR_BA2: U3.N6 (PS_DDR_BA2_502), U7.M3 (BA2)
/RAM/DDR_DQ0: U3.D4 (PS_DDR_DQ0_502), U7.E3 (DQ0)
/RAM/DDR_DQ1: U3.A2 (PS_DDR_DQ1_502), U7.F7 (DQ1)
/RAM/DDR_DQ2: U3.C4 (PS_DDR_DQ2_502), U7.F2 (DQ2)
/RAM/DDR_DQ3: U3.C1 (PS_DDR_DQ3_502), U7.F8 (DQ3)
/RAM/DDR_DQ4: U3.B4 (PS_DDR_DQ4_502), U7.H3 (DQ4)
/RAM/DDR_DQ5: U3.A4 (PS_DDR_DQ5_502), U7.H8 (DQ5)
/RAM/DDR_DQ6: U3.C3 (PS_DDR_DQ6_502), U7.G2 (DQ6)
/RAM/DDR_DQ7: U3.A3 (PS_DDR_DQ7_502), U7.H7 (DQ7)
/RAM/DDR_DQ8: U3.E1 (PS_DDR_DQ8_502), U7.D7 (DQ8)
/RAM/DDR_DQ9: U3.D1 (PS_DDR_DQ9_502), U7.C3 (DQ9)
/RAM/DDR_DQ10: U3.E2 (PS_DDR_DQ10_502), U7.C8 (DQ10)
/RAM/DDR_DQ11: U3.E3 (PS_DDR_DQ11_502), U7.C2 (DQ11)
/RAM/DDR_DQ13: U3.G1 (PS_DDR_DQ13_502), U7.A2 (DQ13)
/RAM/DDR_DQ14: U3.H1 (PS_DDR_DQ14_502), U7.B8 (DQ14)
/RAM/DDR_DQ15: U3.H2 (PS_DDR_DQ15_502), U7.A3 (DQ15)
/RAM/DDR_QD12: U3.F3 (PS_DDR_DQ12_502), U7.A7 (DQ12)
/RAM/DDR_VREF: U3.F4 (PS_DDR_VREF0_502), U7.H1 (VREFDQ), U7.M8 (VREFCA)
/RAM/LDM: U3.B1 (PS_DDR_DM0_502), U7.E7 (LDM)
/RAM/LDQS: U3.C2 (PS_DDR_DQS_P0_502), U7.F3 (LDQS)
/RAM/ODT: U3.K3 (PS_DDR_ODT_502), U7.K1 (ODT)
/RAM/UDM: U3.D3 (PS_DDR_DM1_502), U7.D3 (UDM)
/RAM/UDQS: U3.G2 (PS_DDR_DQS_P1_502), U7.C7 (UDQS)
/RAM/~CAS: U3.R5 (PS_DDR_CAS_B_502), U7.K3 (~CAS)
/RAM/~CK: U3.N2 (PS_DDR_CKN_502), U7.K7 (~CK)
/RAM/~CS: U3.R2 (PS_DDR_CS_B_502), U7.L2 (~CS)
/RAM/~LDQS: U3.B2 (PS_DDR_DQS_N0_502), U7.G3 (~LDQS)
/RAM/~RAS: U3.R6 (PS_DDR_RAS_B_502), U7.J3 (~RAS)
/RAM/~RESET: U3.L4 (PS_DDR_DRST_B_502), U7.T2 (~RESET)
/RAM/~UDQS: U3.F2 (PS_DDR_DQS_N1_502), U7.B7 (~UDQS)
/RAM/~WE: U3.R3 (PS_DDR_WE_B_502), U7.L3 (~WE)
GND: C1.2, C2.2, C4.2, C8.2, C9.2, C10.2, C12.2, C13.2, C14.2, C15.2, C16.2, C17.2, C19.2, C20.2, C21.2, C22.2, C23.2, C24.2, C25.2, C26.2, C27.2, FB2.2, R2.1, R5.1, R8.2, R14.1, R15.1, R16.1, R17.1, R20.1, R22.2, R30.1, R32.1, R34.1, U1.2 (PGND), U1.4 (AGND), U1.7 (PGND), U1.8 (PGND), U2.2 (PGND), U2.4 (AGND), U2.7 (PGND), U2.8 (PGND), U3.A1 (GND), U3.A11 (GND), U3.B8 (GND), U3.C5 (GND), U3.C15 (GND), U3.D2 (GND), U3.D12 (GND), U3.E5 (GND), U3.E7 (GND), U3.E8 (RSVDGND), U3.E9 (GND), U3.F10 (GND), U3.G3 (GND), U3.G5 (GND), U3.G13 (GND), U3.H6 (GND), U3.H10 (GND), U3.J5 (GND), U3.J9 (GND), U3.K4 (GND), U3.K7 (GND), U3.K10 (GND), U3.K14 (GND), U3.L1 (GND), U3.L5 (GND), U3.L11 (GND), U3.M8 (GND), U3.N5 (GND), U3.N15 (GND), U3.P2 (GND), U3.P12 (GND), U3.R9 (GND), U4.2 (GND), U5.4 (GND), U6.6, U6.G1, U6.G2, U6.G3, U7.A9 (VSS), U7.B1 (VSSQ), U7.B3 (VSS), U7.B9 (VSSQ), U7.D1 (VSSQ), U7.D8 (VSSQ), U7.E1 (VSS), U7.E2 (VSSQ), U7.E8 (VSSQ), U7.F9 (VSSQ), U7.G1 (VSSQ), U7.G8 (VSS), U7.G9 (VSSQ), U7.J2 (VSS), U7.J8 (VSS), U7.M1 (VSS), U7.M7 (A15), U7.M9 (VSS), U7.P1 (VSS), U7.P9 (VSS), U7.T1 (VSS), U7.T9 (VSS), U7#2.B3 (VSS), U7#2.C1 (VSSQ), U7#2.E5 (VSSQ), U8.B3 (VSS), U8.C1 (VSSQ), U8.E5 (VSSQ), U8#2.2 (PGND), U8#2.4 (AGND), U8#2.7 (PGND), U8#2.8 (PGND), X1.2 (GND)
GNDA: C18.2, FB2.1, U3.F8 (GNDADC_0), U3.G8 (VREFN_0), U3.H7 (VREFP_0)
MIO7: D2.2 (A), R20.2, U3.D9 (PS_MIO7_500)
MIO28: U3.A15 (PS_MIO28_501), U6.5
MIO29: R26.2, U3.D11 (PS_MIO29_501), U6.3
MIO30: R27.2, U3.B15 (PS_MIO30_501), U6.7
MIO31: R28.2, U3.C12 (PS_MIO31_501), U6.8
MIO32: R24.2, U3.E15 (PS_MIO32_501), U6.1
MIO33: R25.2, U3.C11 (PS_MIO33_501), U6.2
unnamed: C1.1, U6.4
unnamed: D1.1 (K), R13.1
unnamed: D2.1 (K), R22.1
unnamed: R23.2, U6.G4
unnamed: R6.1, TP1.1, U2.11 (PG)
unnamed: R4.1, TP2.1, U1.11 (PG)
unnamed: R31.1, TP6.1, U8#2.11 (PG)
unnamed: C5.2, R1.1, R2.2, U1.5 (FB)
unnamed: C11.2, R3.1, R5.2, U2.5 (FB)
unnamed: R13.2, U3.M7 (DONE_0)
unnamed: R11.2, U3.D5 (INIT_B_0)
unnamed: R12.2, U3.K6 (PROGRAM_B_0)
unnamed: R21.1, U3.C7 (PS_CLK_500)
unnamed: R14.2, U3.B6 (PS_MIO8_500)
unnamed: R34.2, U3.J3 (PS_DDR_VRN_502)
unnamed: R33.2, U3.H3 (PS_DDR_VRP_502)
unnamed: R8.1, R9.1, U4.4 (SENSE)
unnamed: R32.2, U7.L8 (ZQ)
unnamed: C3.2, R29.1, R30.2, U8#2.5 (FB)
unnamed: FB3.2, X1.4 (Vcc)
POR_B: R10.1, U3.C9 (PS_POR_B_500), U4.1 (*RSTVDD), U4.5 (*RSTSENSE)
RAM_CLK: U7#2.B2 (CK), U8.B2 (CK)
RAM_DQ0: U7#2.D3 (DQ0), U8.D3 (DQ0)
RAM_DQ1: U7#2.D2 (DQ1), U8.D2 (DQ1)
RAM_DQ2: U7#2.C4 (DQ2), U8.C4 (DQ2)
RAM_DQ3: U7#2.D4 (DQ3), U8.D4 (DQ3)
RAM_DQ4: U7#2.D5 (DQ4), U8.D5 (DQ4)
RAM_DQ5: U7#2.E3 (DQ5), U8.E3 (DQ5)
RAM_DQ6: U7#2.E2 (DQ6), U8.E2 (DQ6)
RAM_DQ7: U7#2.E1 (DQ7), U8.E1 (DQ7)
RWDS: U7#2.C3 (RWDS), U8.C3 (RWDS)
SPI-CLK: R15.2, U3.A10 (PS_MIO6_500), U5.6 (CLK)
SPI-CS: U3.A5 (PS_MIO1_500), U5.1 (~CS)
SPI-D0: R16.2, U3.A8 (PS_MIO2_500), U5.5 (DI(IO0))
SPI-D1: R17.2, U3.A7 (PS_MIO3_500), U5.2 (DO(IO1))
SPI-D2: R18.2, U3.C8 (PS_MIO4_500), U5.3 (IO2)
SPI-D3: R19.2, U3.A9 (PS_MIO5_500), U5.7 (IO3)
VCCQ: C18.1, FB1.1, U3.F7 (VCCADC_0)
~RAM_CLK: U7#2.B1 (CK#), U8.B1 (CK#)
~RAM_RST: U7#2.A4 (RESET#), U8.A4 (RESET#)
~RST: R7.1, U4.3 (*MR)

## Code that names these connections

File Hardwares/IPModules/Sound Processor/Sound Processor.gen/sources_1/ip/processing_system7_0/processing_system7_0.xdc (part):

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############################################################################

set_property iostandard "SSTL15_T_DCI" [get_ports "DDR_VRP"]
set_property PACKAGE_PIN "H3" [get_ports "DDR_VRP"]
set_property slew "FAST" [get_ports "DDR_VRP"]
set_property PIO_DIRECTION "BIDIR" [get_ports "DDR_VRP"]
set_property iostandard "SSTL15_T_DCI" [get_ports "DDR_VRN"]
set_property PACKAGE_PIN "J3" [get_ports "DDR_VRN"]
set_property slew "FAST" [get_ports "DDR_VRN"]
set_property PIO_DIRECTION "BIDIR" [get_ports "DDR_VRN"]
set_property iostandard "SSTL15" [get_ports "DDR_WEB"]
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set_property slew "SLOW" [get_ports "DDR_RAS_n"]
set_property PIO_DIRECTION "OUTPUT" [get_ports "DDR_RAS_n"]
set_property iostandard "SSTL15" [get_ports "DDR_ODT"]
set_property PACKAGE_PIN "K3" [get_ports "DDR_ODT"]
set_property slew "SLOW" [get_ports "DDR_ODT"]
set_property PIO_DIRECTION "OUTPUT" [get_ports "DDR_ODT"]
set_property iostandard "SSTL15" [get_ports "DDR_DRSTB"]
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set_property slew "SLOW" [get_ports "DDR_CS_n"]
set_property PIO_DIRECTION "OUTPUT" [get_ports "DDR_CS_n"]
set_property iostandard "SSTL15" [get_ports "DDR_CKE"]
set_property PACKAGE_PIN "L3" [get_ports "DDR_CKE"]
set_property slew "SLOW" [get_ports "DDR_CKE"]
set_property PIO_DIRECTION "OUTPUT" [get_ports "DDR_CKE"]
set_property iostandard "DIFF_SSTL15" [get_ports "DDR_Clk"]
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set_property PACKAGE_PIN "B11" [get_ports "PS_SRSTB"]
set_property slew "fast" [get_ports "PS_SRSTB"]
set_property iostandard "LVCMOS33" [get_ports "PS_CLK"]
set_property PACKAGE_PIN "C7" [get_ports "PS_CLK"]
set_property slew "fast" [get_ports "PS_CLK"]


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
